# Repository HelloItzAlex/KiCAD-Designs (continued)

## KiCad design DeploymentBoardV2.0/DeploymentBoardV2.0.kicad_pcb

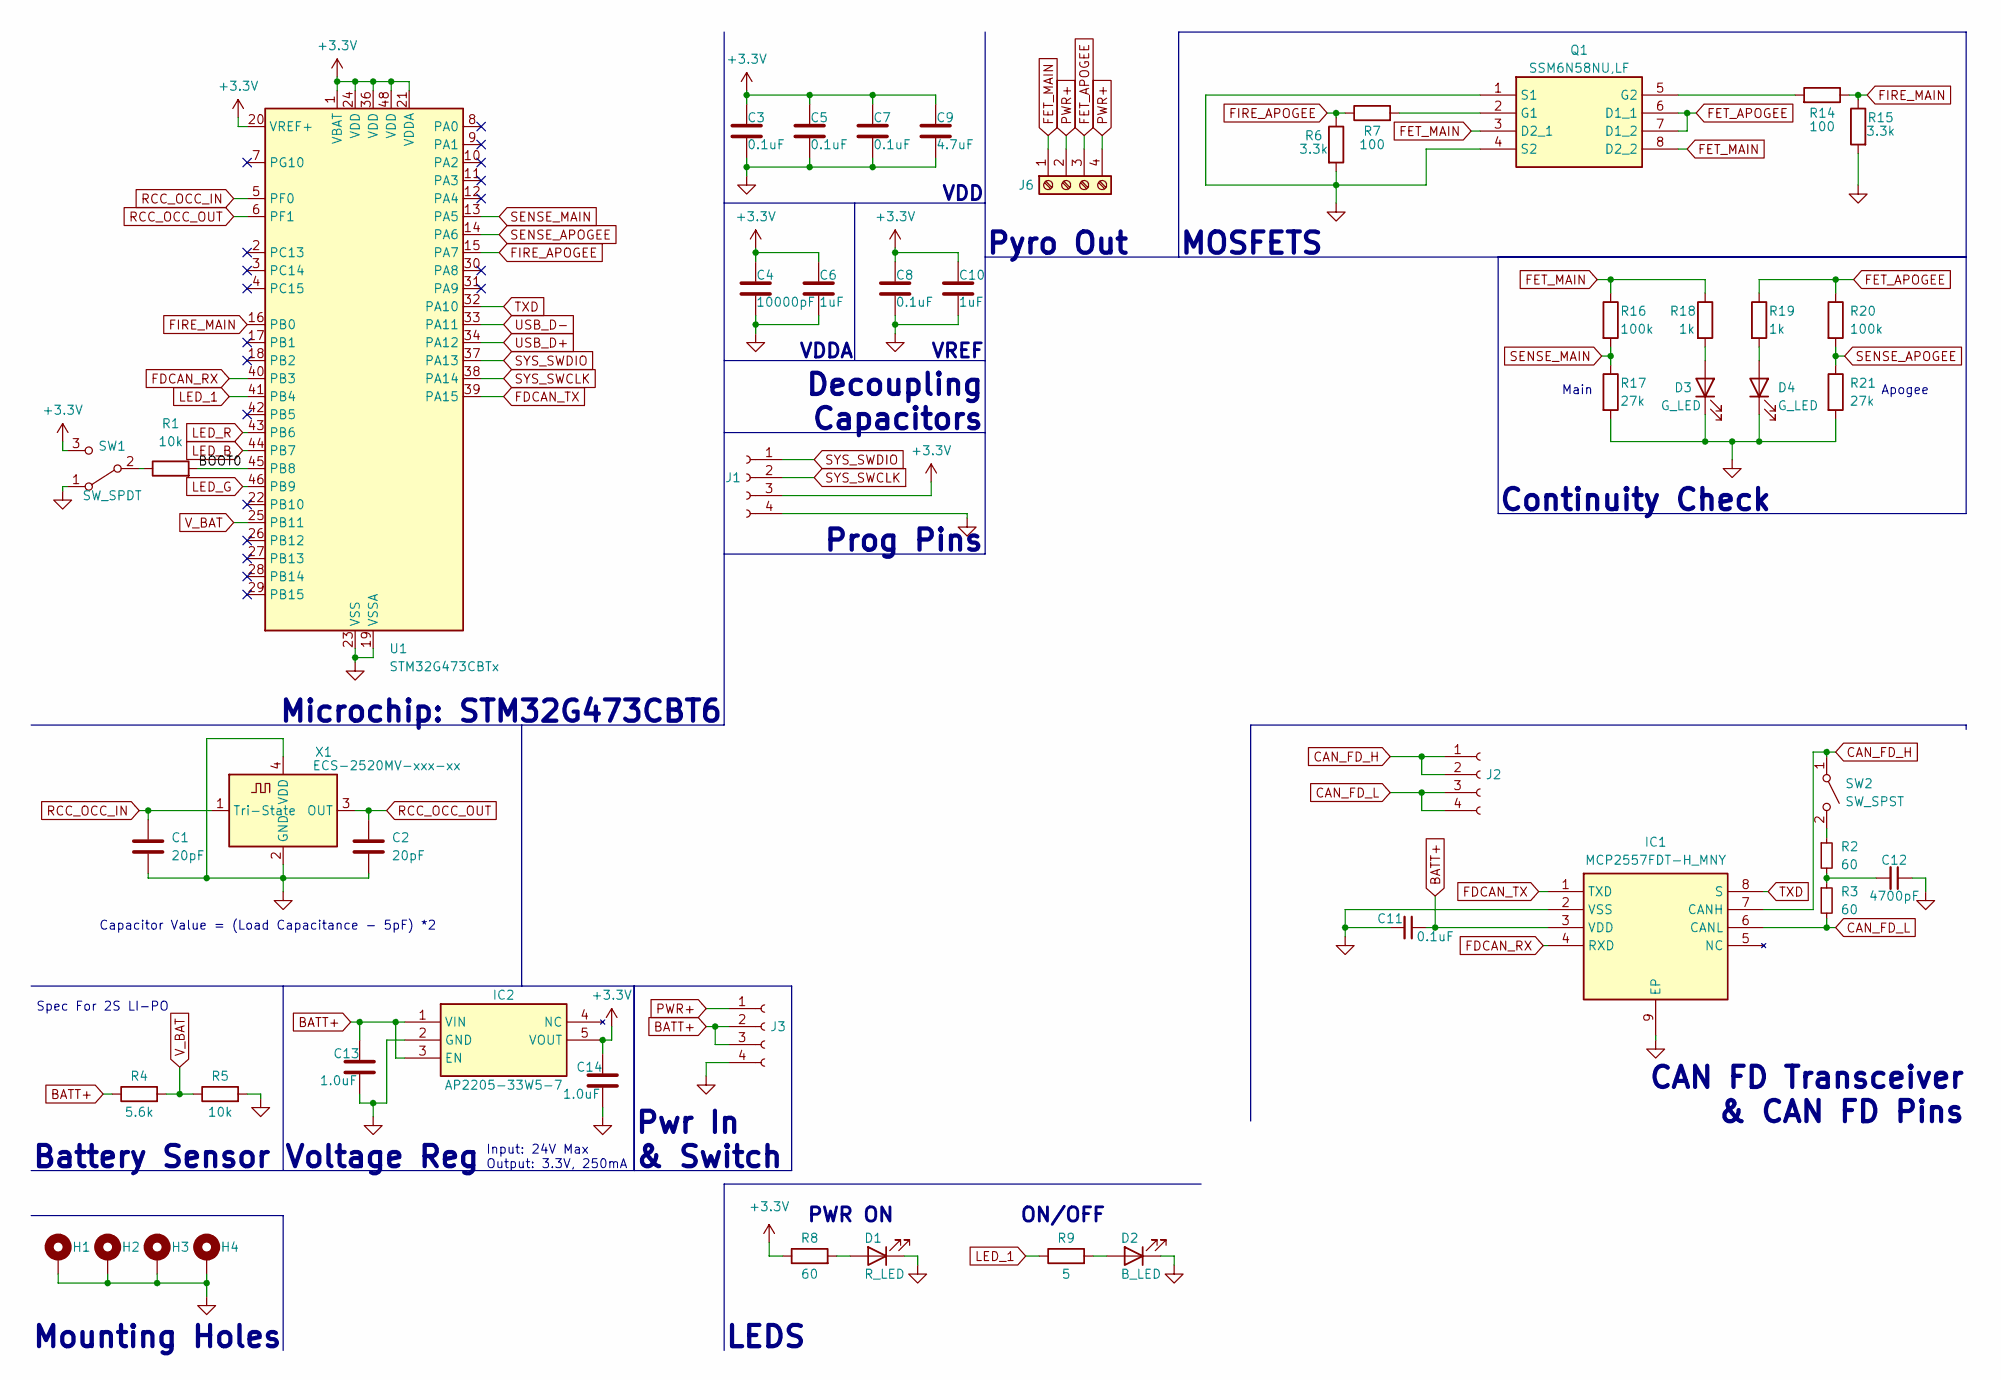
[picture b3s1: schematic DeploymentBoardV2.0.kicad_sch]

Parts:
C1, C2: 20pF; C_0402_1005Metric
C3, C5, C7, C8, C11: 0.1uF; C_0402_1005Metric
C4: 10000pF; C_0402_1005Metric
C6, C10: 1uF; C_0603_1608Metric
C9: 4.7uF; C_0603_1608Metric
C12: 4700pF; C_0402_1005Metric
C13, C14: 1.0uF; C_0402_1005Metric
D1: R_LED; LED_0402_1005Metric
D2: B_LED; LED_0402_1005Metric
D3, D4: G_LED; LED_0402_1005Metric
H1, H2, H3, H4: MountingHole_Pad; MountingHole_2.2mm_M2_ISO7380_Pad
IC1: MCP2557FDT-H_MNY; SON50P300X200X80-9N-D; Mouser Part Number 579-MCP2557FDT-H/MNY
IC2: AP2205-33W5-7; SOT95P282X130-5N; Mouser Part Number 621-AP2205-33W5-7
J1, J2, J3: Conn_01x04_Socket; PinHeader_1x04_P2.54mm_Vertical
J6: PYRO CHANNELS; TerminalBlock_Phoenix_MPT-0,5-4-2.54_1x04_P2.54mm_Horizontal
Q1: SSM6N58NU,LF; SSM6N58NULF; Mouser Part Number 757-SSM6N58NULF
R1, R5: 10k; R_0402_1005Metric
R2, R3: 60; R_0805_2012Metric
R4: 5.6k; R_0402_1005Metric
R6, R15: 3.3k; R_0402_1005Metric
R7, R14: 100; R_0402_1005Metric
R8: 60; R_0402_1005Metric
R9: 5; R_0402_1005Metric
R16, R20: 100k; R_0402_1005Metric
R17, R21: 27k; R_0402_1005Metric
R18, R19: 1k; R_0402_1005Metric
SW1: SW_SPDT; SolderJumper-3_P1.3mm_Open_RoundedPad1.0x1.5mm_NumberLabels
SW2: SW_SPST; SolderJumper-2_P1.3mm_Open_RoundedPad1.0x1.5mm
U1: STM32G473CBTx; LQFP-48_7x7mm_P0.5mm
X1: ECS-2520MV-xxx-xx; Oscillator_SMD_ECS_2520MV-xxx-xx-4Pin_2.5x2.0mm

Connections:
+3.3V: C3.1, C4.1, C5.1, C6.1, C7.1, C8.1, C9.1, C10.1, C14.1, IC2.5 (VOUT), J1.3, R8.1, SW1.3 (C), U1.1 (VBAT), U1.20 (VREF+), U1.21 (VDDA), U1.24 (VDD), U1.36 (VDD), U1.48 (VDD)
/BOOT0: R1.2, U1.45 (PB8)
BATT+: C11.1, C13.1, IC1.3 (VDD), IC2.1 (VIN), IC2.3 (EN), J3.2, J3.3, R4.1
CAN_FD_H: IC1.7 (CANH), J2.1, J2.2, SW2.1 (A)
CAN_FD_L: IC1.6 (CANL), J2.3, J2.4, R3.2
FDCAN_RX: IC1.4 (RXD), U1.40 (PB3)
FDCAN_TX: IC1.1 (TXD), U1.39 (PA15)
FET_APOGEE: J6.3, Q1.6 (D1_1), Q1.7 (D1_2), R19.1, R20.1
FET_MAIN: J6.1, Q1.3 (D2_1), Q1.8 (D2_2), R16.1, R18.1
FIRE_APOGEE: R6.1, R7.1, U1.15 (PA7)
FIRE_MAIN: R14.1, R15.1, U1.16 (PB0)
GND: C1.2, C2.2, C3.2, C4.2, C5.2, C6.2, C7.2, C8.2, C9.2, C10.2, C11.2, C12.1, C13.2, C14.2, D1.1 (K), D2.1 (K), D3.1 (K), D4.1 (K), H1.1, H2.1, H3.1, H4.1, IC1.2 (VSS), IC1.9 (EP), IC2.2 (GND), J1.4, J3.4, Q1.1 (S1), Q1.4 (S2), R5.2, R6.2, R15.2, R17.2, R21.2, SW1.1 (A), U1.19 (VSSA), U1.23 (VSS), U1.35 (VSS), U1.47 (VSS), X1.2 (GND), X1.4 (VDD)
LED_1: R9.1, U1.41 (PB4)
LED_B: U1.44 (PB7)
LED_G: U1.46 (PB9)
LED_R: U1.43 (PB6)
unnamed: C12.2, R2.2, R3.1
unnamed: D1.2 (A), R8.2
unnamed: D2.2 (A), R9.2
unnamed: D3.2 (A), R18.2
unnamed: D4.2 (A), R19.2
unnamed: Q1.2 (G1), R7.2
unnamed: Q1.5 (G2), R14.2
unnamed: R1.1, SW1.2 (B)
unnamed: R2.1, SW2.2 (B)
PWR+: J3.1, J6.2, J6.4
RCC_OCC_IN: C1.1, U1.5 (PF0), X1.1 (Tri-State)
RCC_OCC_OUT: C2.1, U1.6 (PF1), X1.3 (OUT)
SENSE_APOGEE: R20.2, R21.1, U1.14 (PA6)
SENSE_MAIN: R16.2, R17.1, U1.13 (PA5)
SYS_SWCLK: J1.2, U1.38 (PA14)
SYS_SWDIO: J1.1, U1.37 (PA13)
TXD: IC1.8 (S), U1.32 (PA10)
USB_D+: U1.34 (PA12)
USB_D-: U1.33 (PA11)
V_BAT: R4.2, R5.1, U1.25 (PB11)

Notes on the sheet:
Pyro Out
Spec For 2S LI-PO
Decoupling Capacitors
LEDS
Main
MOSFETS
VDD
Capacitor Value = (Load Capacitance - 5pF) *2
Microchip: STM32G473CBT6
Continuity Check
Mounting Holes
Battery Sensor
Apogee
Voltage Reg
Pwr In & Switch
CAN FD Transceiver & CAN FD Pins
Prog Pins
Input: 24V Max Output: 3.3V, 250mA
PWR ON
VDDA
ON/OFF
VREF

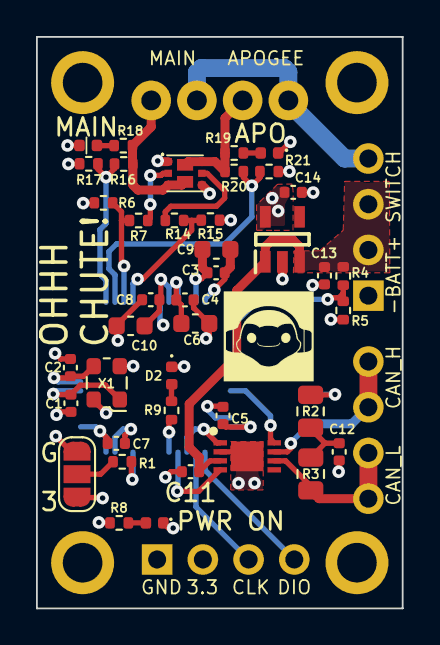
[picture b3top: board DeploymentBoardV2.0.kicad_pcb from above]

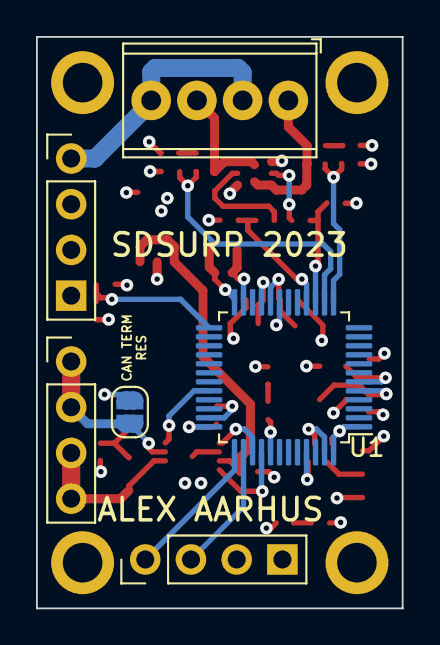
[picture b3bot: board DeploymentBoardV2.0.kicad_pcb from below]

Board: 4 copper layers, 20.3 x 31.8 mm, 50 parts (6 on the bottom side), 31 nets.

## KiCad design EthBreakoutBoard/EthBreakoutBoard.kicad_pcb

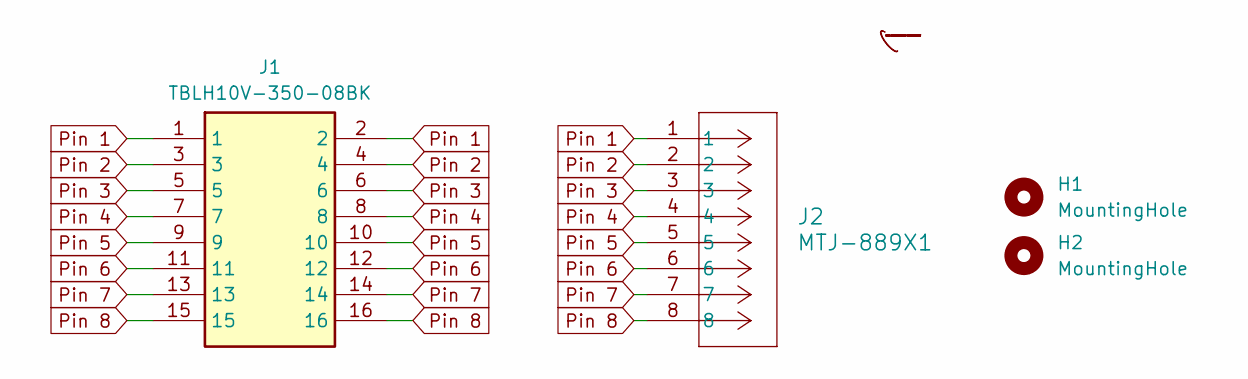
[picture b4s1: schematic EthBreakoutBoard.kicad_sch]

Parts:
H1, H2: MountingHole; MountingHole_3.2mm_M3
J1: TBLH10V-350-08BK; RHDR16W80P550X350_2X8_2870X850X1420P; Mouser Part Number 490-TBLH10V-350-08BK
J2: MTJ-889X1; CONN_MTJ-889X1_ADM

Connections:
Pin 1: J1.1, J1.2, J2.1
Pin 2: J1.3, J1.4, J2.2
Pin 3: J1.5, J1.6, J2.3
Pin 4: J1.7, J1.8, J2.4
Pin 5: J1.9, J1.10, J2.5
Pin 6: J1.11, J1.12, J2.6
Pin 7: J1.13, J1.14, J2.7
Pin 8: J1.15, J1.16, J2.8

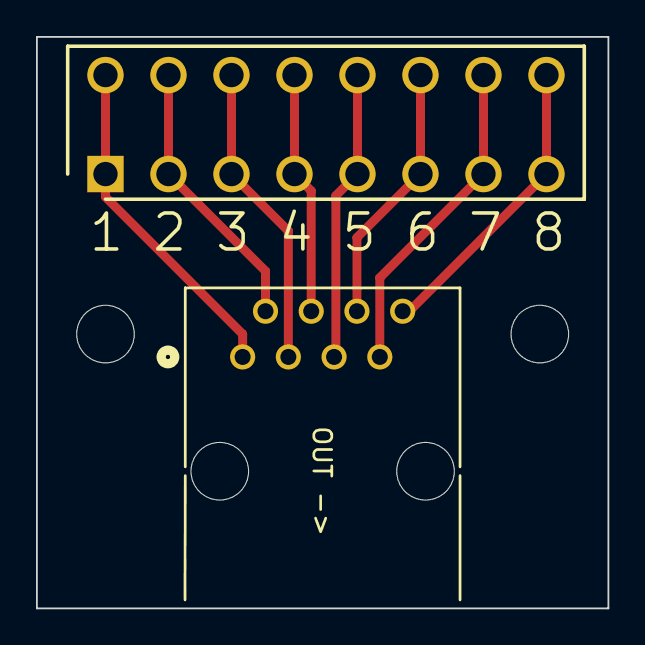
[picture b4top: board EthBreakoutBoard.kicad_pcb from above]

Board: 2 copper layers, 31.8 x 31.8 mm, 4 parts (0 on the bottom side), 8 nets.

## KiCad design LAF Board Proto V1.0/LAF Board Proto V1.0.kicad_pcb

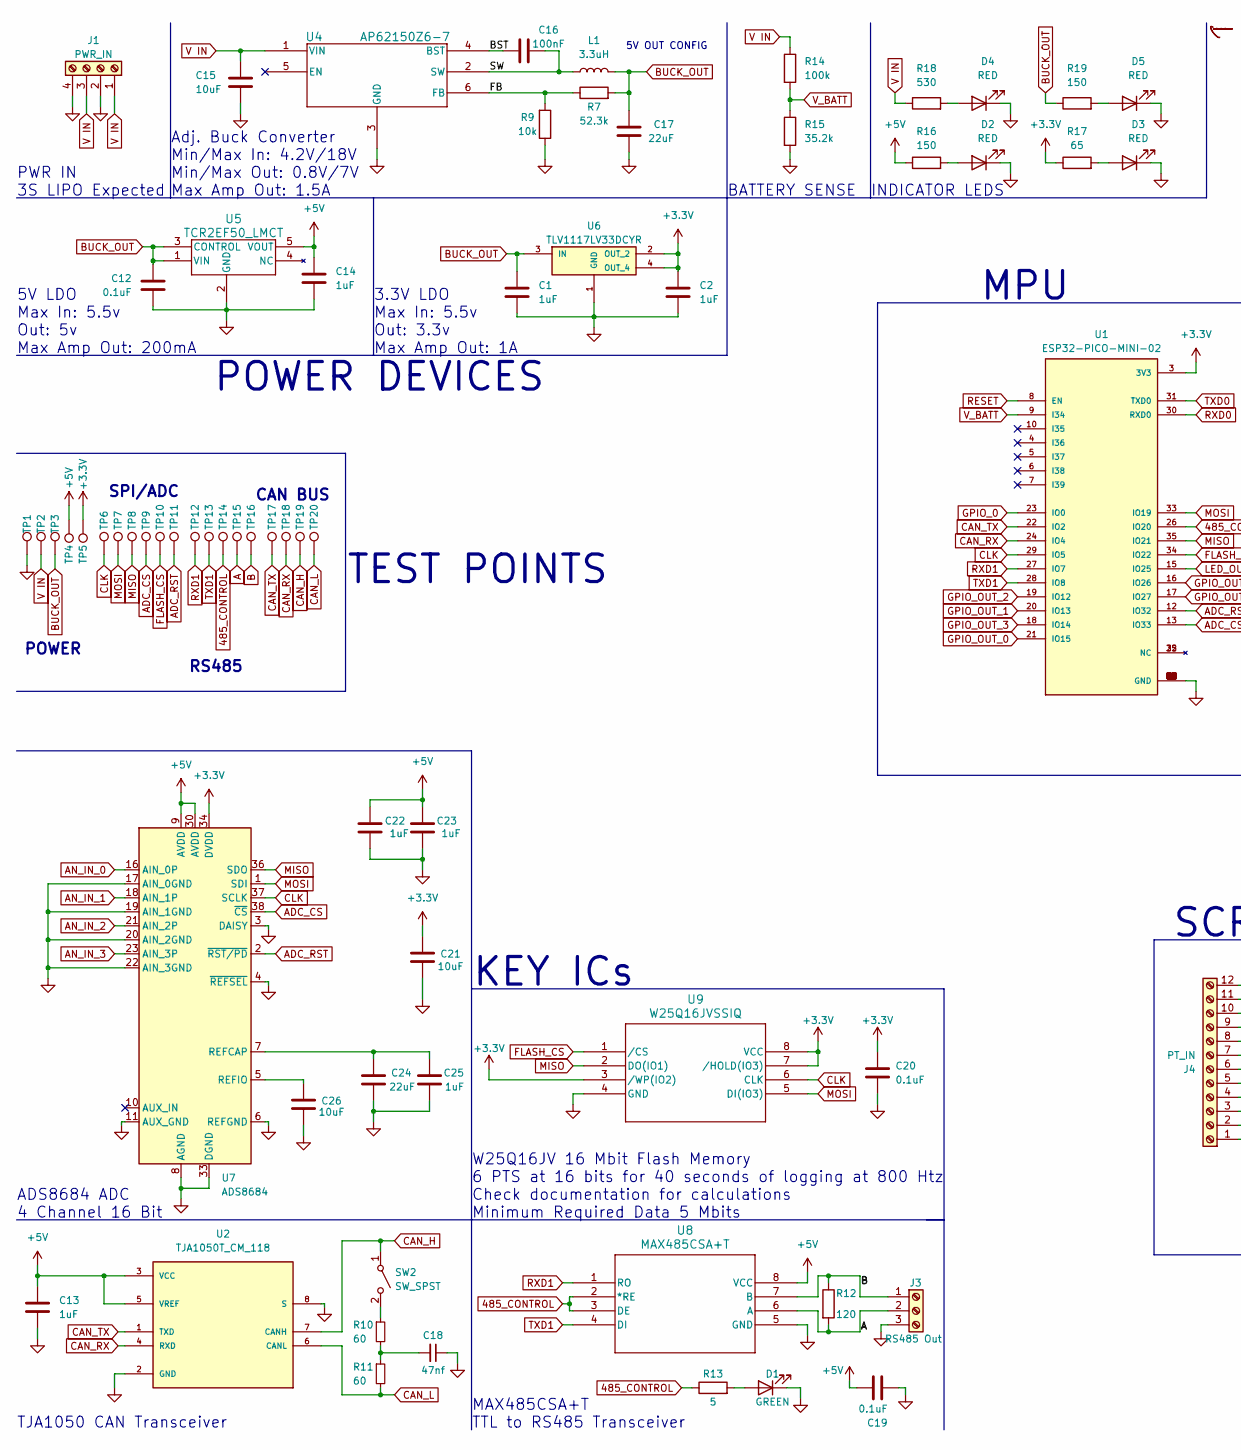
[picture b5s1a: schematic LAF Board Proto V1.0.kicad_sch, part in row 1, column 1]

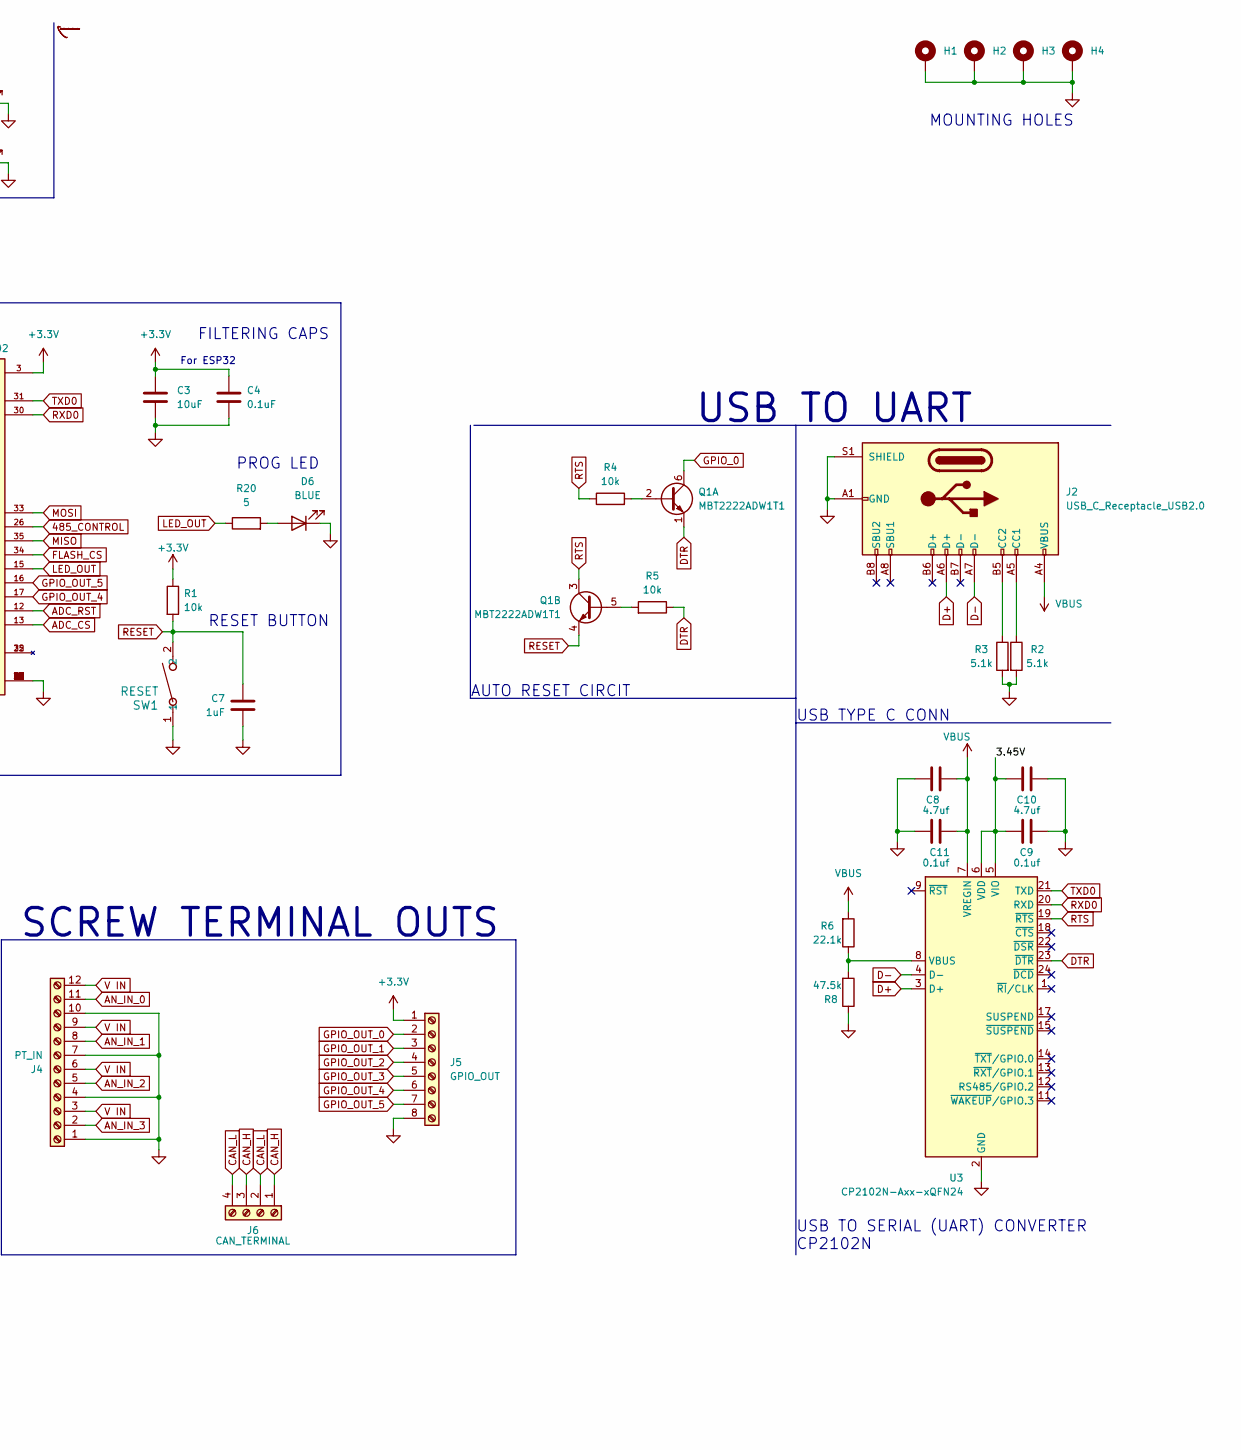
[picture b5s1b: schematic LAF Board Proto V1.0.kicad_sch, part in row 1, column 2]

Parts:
C1, C7, C14, C22, C23, C25: 1uF; C_0603_1608Metric
C2: 1uF; C_0805_2012Metric
C3, C21: 10uF; C_0805_2012Metric
C4, C12: 0.1uF; C_0603_1608Metric
C8, C10: 4.7uf; C_0402_1005Metric
C9, C11: 0.1uf; C_0402_1005Metric
C13: 1uF; C_0402_1005Metric
C15: 10uF; C_0402_1005Metric
C16: 100nF; C_0402_1005Metric
C17: 22uF; C_0402_1005Metric
C18: 47nf; C_0402_1005Metric
C19, C20: 0.1uF; C_0402_1005Metric
C24: 22uF; C_1210_3225Metric
C26: 10uF; C_0603_1608Metric
D1: GREEN; LED_0603_1608Metric
D2, D3, D4, D5: RED; LED_0603_1608Metric
D6: BLUE; LED_0603_1608Metric
H1, H2, H3, H4: MountingHole_Pad; MountingHole_3.2mm_M3_DIN965_Pad
J1: PWR_IN; TerminalBlock_Phoenix_MPT-0,5-4-2.54_1x04_P2.54mm_Horizontal
J2: USB_C_Receptacle_USB2.0; USB_C_Receptacle_HCTL_HC-TYPE-C-16P-01A
J3: RS485 Out; TerminalBlock_Phoenix_MPT-0,5-3-2.54_1x03_P2.54mm_Horizontal
J4: PT_IN; TerminalBlock_Phoenix_MPT-0,5-12-2.54_1x12_P2.54mm_Horizont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
J5: GPIO_OUT; TerminalBlock_Phoenix_MPT-0,5-8-2.54_1x08_P2.54mm_Horizontal
J6: CAN_TERMINAL; TerminalBlock_Phoenix_MPT-0,5-4-2.54_1x04_P2.54mm_Horizontal
L1: 3.3uH; L_1008_2520Metric
Q1: MBT2222ADW1T1; SOT-363_SC-70-6
R1, R4, R5, R9: 10k; R_0402_1005Metric
R2, R3: 5.1k; R_0402_1005Metric
R6: 22.1k; R_0402_1005Metric
R7: 52.3k; R_0402_1005Metric
R8: 47.5k; R_0402_1005Metric
R10, R11: 60; R_0805_2012Metric
R12: 120; R_0805_2012Metric
R13, R20: 5; R_0402_1005Metric
R14: 100k; R_0402_1005Metric
R15: 35.2k; R_0402_1005Metric
R16, R19: 150; R_0402_1005Metric
R17: 65; R_0402_1005Metric
R18: 530; R_0402_1005Metric
SW1: RESET; SW_PTS636_CNK
SW2: SW_SPST; SolderJumper-2_P1.3mm_Open_RoundedPad1.0x1.5mm
TP1, TP2, TP3, TP4, TP5, TP6, TP7, TP8, TP9, TP10, TP11, TP12, TP13, TP14, TP15, TP16, TP17, TP18, TP19, TP20: TestPoint; TestPoint_Loop_D1.80mm_Drill1.0mm_Beaded
U1: ESP32-PICO-MINI-02; MODULE_ESP32-PICO-MINI-02; PARTREV v1.0
U2: TJA1050T_CM_118; SOIC127P600X175-8N; PARTREV 4
U3: CP2102N-Axx-xQFN24; QFN-24-1EP_4x4mm_P0.5mm_EP2.7x2.7mm
U4: AP62150Z6-7; TSOT-23-6
U5: TCR2EF50_LMCT; SOT_EF50_LMCT_TOS
U6: TLV1117LV33DCYR; VREG_TLV1117LV33DCYR; PARTREV B
U7: ADS8684; TSSOP-38_4.4x9.7mm_P0.5mm
U8: MAX485CSA+T; 21-0041-3-M_90-0096-8L_MXM
U9: W25Q16JVSSIQ; W25Q16JVSSIQ_WIN

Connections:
485_CONTROL: R13.1, TP14.1, U1.26 (IO20), U8.2 (*RE), U8.3 (DE)
+3.3V: C2.1, C3.1, C4.1, C20.1, C21.2, J5.1, R1.1, R17.1, TP5.1, U1.3 (3V3), U6.2 (OUT_2), U6.4 (OUT_4), U7.34 (DVDD), U9.3 (/WP(IO2)), U9.7 (/HOLD(IO3)), U9.8 (VCC)
+5V: C13.1, C14.1, C19.1, C22.2, C23.2, R16.1, TP4.1, U2.3 (VCC), U2.5 (VREF), U5.5 (VOUT), U7.9 (AVDD), U7.30 (AVDD), U8.8 (VCC)
/3.45V: C9.1, C10.1, U3.5 (VIO), U3.6 (VDD)
/BST: C16.1, U4.4 (BST)
/FB: R7.1, R9.2, U4.6 (FB)
/SW: C16.2, L1.1, U4.2 (SW)
A: J3.2, R12.2, TP15.1, U8.6 (A)
ADC_CS: TP9.1, U1.13 (IO33), U7.38 (~CS)
ADC_RST: TP11.1, U1.12 (IO32), U7.2 (~RST/PD)
AN_IN_0: J4.11, U7.16 (AIN_0P)
AN_IN_1: J4.8, U7.18 (AIN_1P)
AN_IN_2: J4.5, U7.21 (AIN_2P)
AN_IN_3: J4.2, U7.23 (AIN_3P)
B: J3.1, R12.1, TP16.1, U8.7 (B)
BUCK_OUT: C1.1, C12.1, C17.1, L1.2, R7.2, R19.1, TP3.1, U5.1 (VIN), U5.3 (CONTROL), U6.3 (IN)
CAN_H: J6.1, J6.3, SW2.1 (A), TP19.1, U2.7 (CANH)
CAN_L: J6.2, J6.4, R11.2, TP20.1, U2.6 (CANL)
CAN_RX: TP18.1, U1.24 (IO4), U2.4 (RXD)
CAN_TX: TP17.1, U1.22 (IO2), U2.1 (TXD)
CLK: TP6.1, U1.29 (IO5), U7.37 (SCLK), U9.6 (CLK)
D+: J2.A6 (D+), U3.3 (D+)
D-: J2.A7 (D-), U3.4 (D-)
DTR: Q1.1 (E1), R5.1, U3.23 (~DTR)
FLASH_CS: TP10.1, U1.34 (IO22), U9.1 (/CS)
GND: C1.2, C2.2, C3.2, C4.2, C7.2, C8.2, C9.2, C10.2, C11.2, C12.2, C13.2, C14.2, C15.2, C17.2, C18.1, C19.2, C20.2, C21.1, C22.1, C23.1, C24.1, C25.1, C26.2, D1.1 (K), D2.1 (K), D3.1 (K), D4.1 (K), D5.1 (K), D6.1 (K), H1.1, H2.1, H3.1, H4.1, J1.2, J1.4, J2.A1 (GND), J2.A12 (GND), J2.B1 (GND), J2.B12 (GND), J2.S1 (SHIELD), J3.3, J4.1, J4.4, J4.7, J4.10, J5.8, R2.2, R3.2, R8.1, R9.1, R15.2, SW1.1, TP1.1, U1.1 (GND), U1.2 (GND), U1.11 (GND), U1.14 (GND), U1.36 (GND), U1.37 (GND), U1.38 (GND), U1.39 (GND), U1.40 (GND), U1.41 (GND), U1.42 (GND), U1.43 (GND), U1.44 (GND), U1.45 (GND), U1.46 (GND), U1.47 (GND), U1.48 (GND), U1.49 (GND), U1.50 (GND), U1.51 (GND), U1.52 (GND), U1.53 (GND), U1.54 (GND), U1.55 (GND), U1.56 (GND), U1.57 (GND), U1.58 (GND), U1.59 (GND), U1.60 (GND), U1.61 (GND), U2.2 (GND), U2.8 (S), U3.2 (GND), U3.25 (GND), U4.3 (GND), U5.2 (GND), U6.1 (GND), U7.3 (DAISY), U7.4 (~REFSEL), U7.6 (REFGND), U7.8 (AGND), U7.11 (AUX_GND), U7.17 (AIN_0GND), U7.19 (AIN_1GND), U7.20 (AIN_2GND), U7.22 (AIN_3GND), U7.28 (AGND), U7.29 (AGND), U7.31 (AGND), U7.32 (AGND), U7.33 (DGND), U8.5 (GND), U9.4 (GND)
GPIO_0: Q1.6 (C1), U1.23 (IO0)
GPIO_OUT_0: J5.2, U1.21 (IO15)
GPIO_OUT_1: J5.3, U1.20 (IO13)
GPIO_OUT_2: J5.4, U1.19 (IO12)
GPIO_OUT_3: J5.5, U1.18 (IO14)
GPIO_OUT_4: J5.6, U1.17 (IO27)
GPIO_OUT_5: J5.7, U1.16 (IO26)
LED_OUT: R20.1, U1.15 (IO25)
MISO: TP8.1, U1.35 (IO21), U7.36 (SDO), U9.2 (DO(IO1))
MOSI: TP7.1, U1.33 (IO19), U7.1 (SDI), U9.5 (DI(IO3))
unnamed: C18.2, R10.2, R11.1
unnamed: D1.2 (A), R13.2
unnamed: D2.2 (A), R16.2
unnamed: D3.2 (A), R17.2
unnamed: D4.2 (A), R18.2
unnamed: D5.2 (A), R19.2
unnamed: D6.2 (A), R20.2
unnamed: J2.A5 (CC1), R2.1
unnamed: J2.B5 (CC2), R3.1
unnamed: Q1.2 (B1), R4.2
unnamed: Q1.5 (B2), R5.2
unnamed: R10.1, SW2.2 (B)
unnamed: R6.1, R8.2, U3.8 (VBUS)
unnamed: C24.2, C25.2, U7.7 (REFCAP)
unnamed: C26.1, U7.5 (REFIO)
RESET: C7.1, Q1.4 (E2), R1.2, SW1.2, U1.8 (EN)
RTS: Q1.3 (C2), R4.1, U3.19 (~RTS)
RXD0: U1.30 (RXD0), U3.20 (RXD)
RXD1: TP12.1, U1.27 (IO7), U8.1 (RO)
TXD0: U1.31 (TXD0), U3.21 (TXD)
TXD1: TP13.1, U1.28 (IO8), U8.4 (DI)
V IN: C15.1, J1.1, J1.3, J4.3, J4.6, J4.9, J4.12, R14.1, R18.1, TP2.1, U4.1 (VIN)
VBUS: C8.1, C11.1, J2.A4 (VBUS), J2.A9 (VBUS), J2.B4 (VBUS), J2.B9 (VBUS), R6.2, U3.7 (VREGIN)
V_BATT: R14.2, R15.1, U1.9 (I34)

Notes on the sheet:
BATTERY SENSE
MPU
For ESP32
USB TO UART
TEST POINTS
USB TO SERIAL (UART) CONVERTER CP2102N
RESET BUTTON
POWER
ADS8684 ADC 4 Channel 16 Bit
Adj. Buck Converter Min/Max In: 4.2V/18V Min/Max Out: 0.8V/7V Max Amp Out: 1.5A
SCREW TERMINAL OUTS
W25Q16JV 16 Mbit Flash Memory 6 PTS at 16 bits for 40 seconds of logging at 800 Htz Check documentation for calculations Minimum Required Data 5 Mbits
SPI/ADC
FILTERING CAPS
MAX485CSA+T TTL to RS485 Transceiver
3.3V LDO Max In: 5.5v Out: 3.3v Max Amp Out: 1A
TJA1050 CAN Transceiver
RS485
PROG LED
INDICATOR LEDS
CAN BUS
POWER DEVICES
AUTO RESET CIRCIT
PWR IN 3S LIPO Expected
5V LDO Max In: 5.5v Out: 5v Max Amp Out: 200mA
USB TYPE C CONN
MOUNTING HOLES
5V OUT CONFIG
KEY ICs

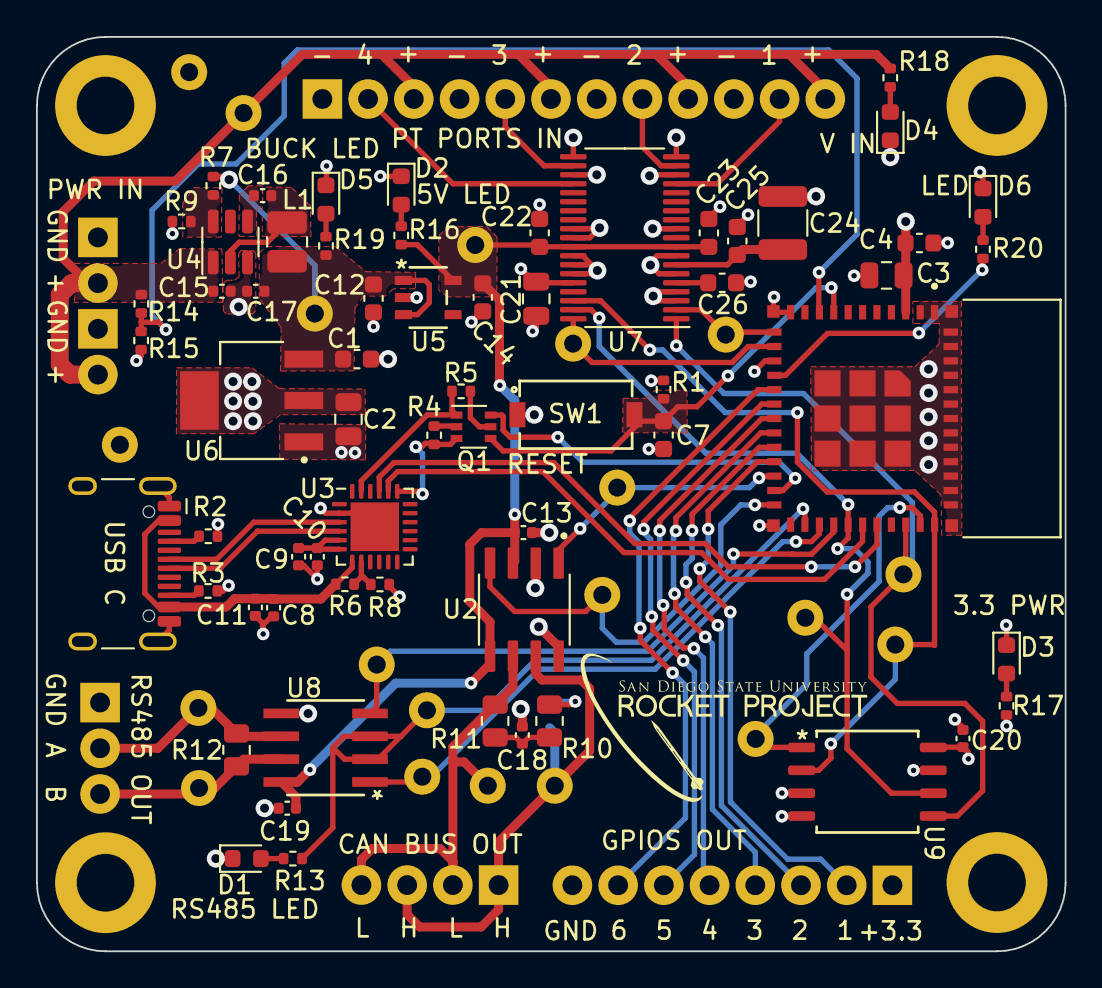
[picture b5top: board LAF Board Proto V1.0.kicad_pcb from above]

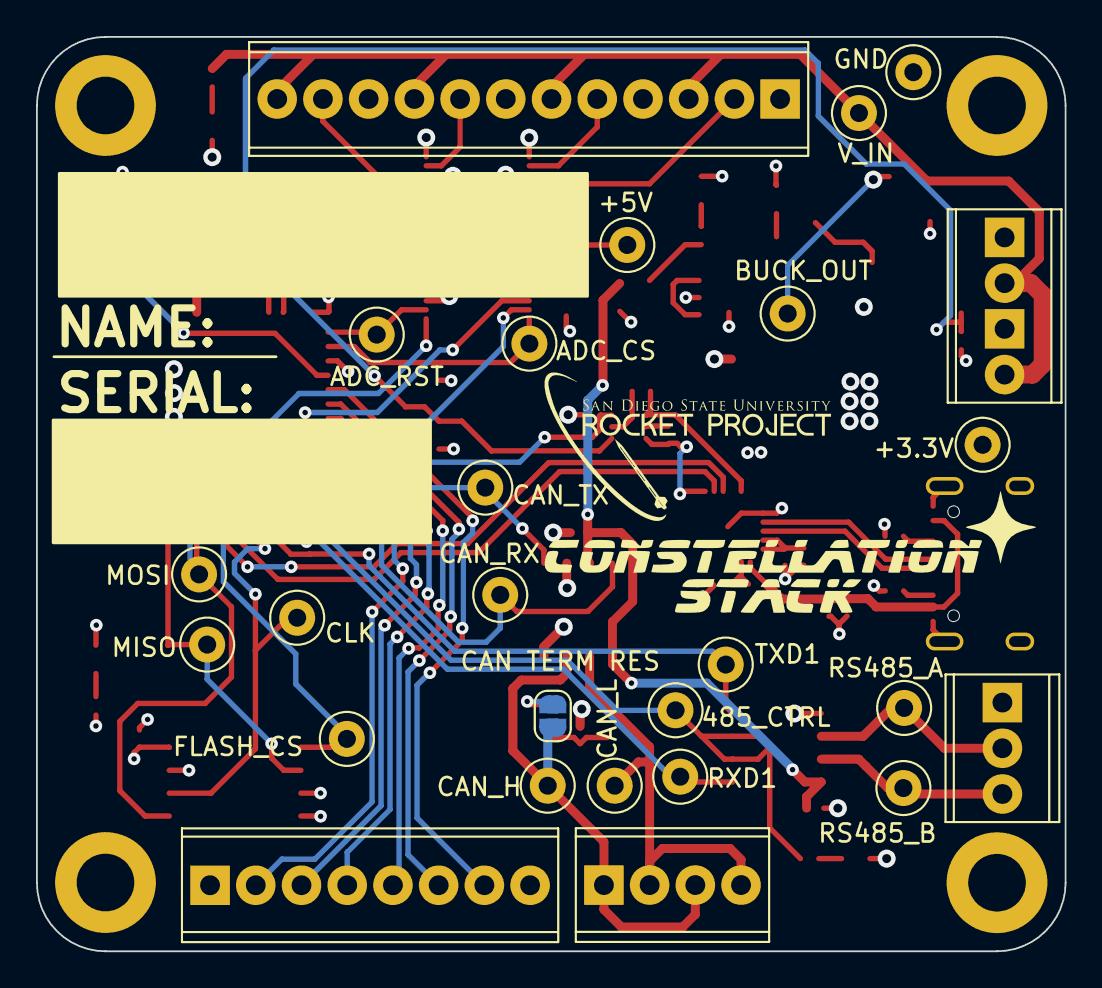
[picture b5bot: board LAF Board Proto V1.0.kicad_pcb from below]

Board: 4 copper layers, 57.1 x 50.8 mm, 93 parts (26 on the bottom side), 60 nets.

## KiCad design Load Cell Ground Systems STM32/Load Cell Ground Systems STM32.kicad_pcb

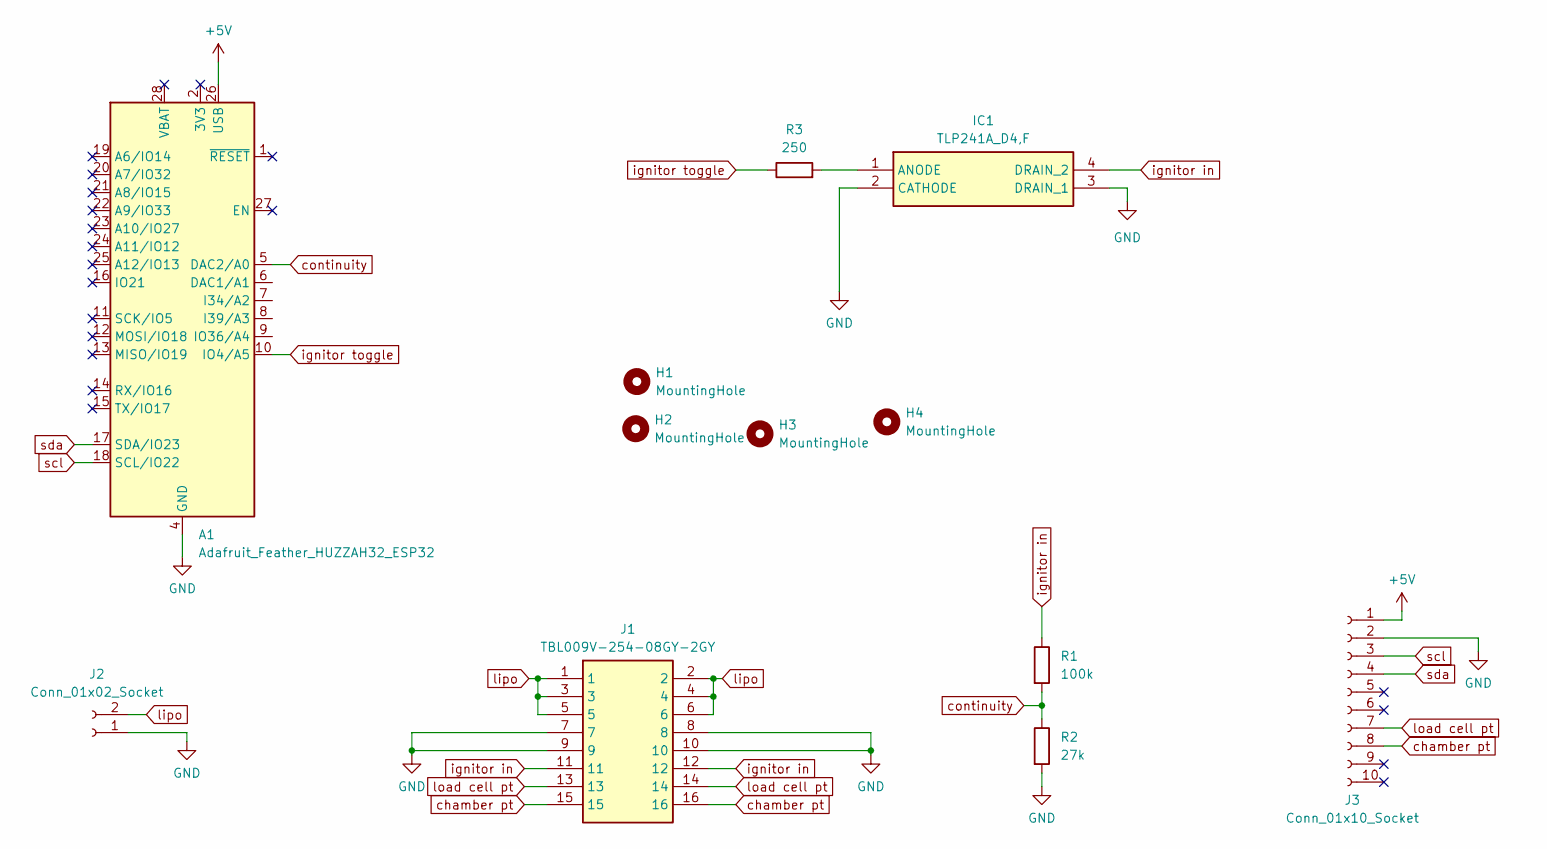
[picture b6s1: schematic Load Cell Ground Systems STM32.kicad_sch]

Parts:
A1: Adafruit_Feather_HUZZAH32_ESP32; Adafruit_Feather
H1, H2, H3, H4: MountingHole; MountingHole_3.2mm_M3
IC1: TLP241A_D4,F; DIP762W60P254L458H485Q4N; Mouser Part Number 757-TLP241AD4F
J1: TBL009V-254-08GY-2GY; RHDR16W70P508X254_2X8_2182X1000X1655P; Mouser Part Number 490-TBL09V25408GY2GY
J2: Conn_01x02_Socket; PinSocket_1x02_P2.54mm_Vertical
J3: Conn_01x10_Socket; PinSocket_1x10_P2.54mm_Vertical
R1: 100k; R_Axial_DIN0204_L3.6mm_D1.6mm_P5.08mm_Horizontal
R2: 27k; R_Axial_DIN0204_L3.6mm_D1.6mm_P5.08mm_Horizontal
R3: 250; R_Axial_DIN0204_L3.6mm_D1.6mm_P5.08mm_Horizontal

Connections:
+5V: A1.26 (USB), J3.1
GND: A1.4 (GND), IC1.2 (CATHODE), IC1.3 (DRAIN_1), J1.7, J1.8, J1.9, J1.10, J2.1, J3.2, R2.2
unnamed: IC1.1 (ANODE), R3.2
chamber pt: J1.15, J1.16, J3.8
continuity: A1.5 (DAC2/A0), R1.2, R2.1
ignitor in: IC1.4 (DRAIN_2), J1.11, J1.12, R1.1
ignitor toggle: A1.10 (IO4/A5), R3.1
lipo: J1.1, J1.2, J1.3, J1.4, J1.5, J1.6, J2.2
load cell pt: J1.13, J1.14, J3.7
scl: A1.18 (SCL/IO22), J3.3
sda: A1.17 (SDA/IO23), J3.4

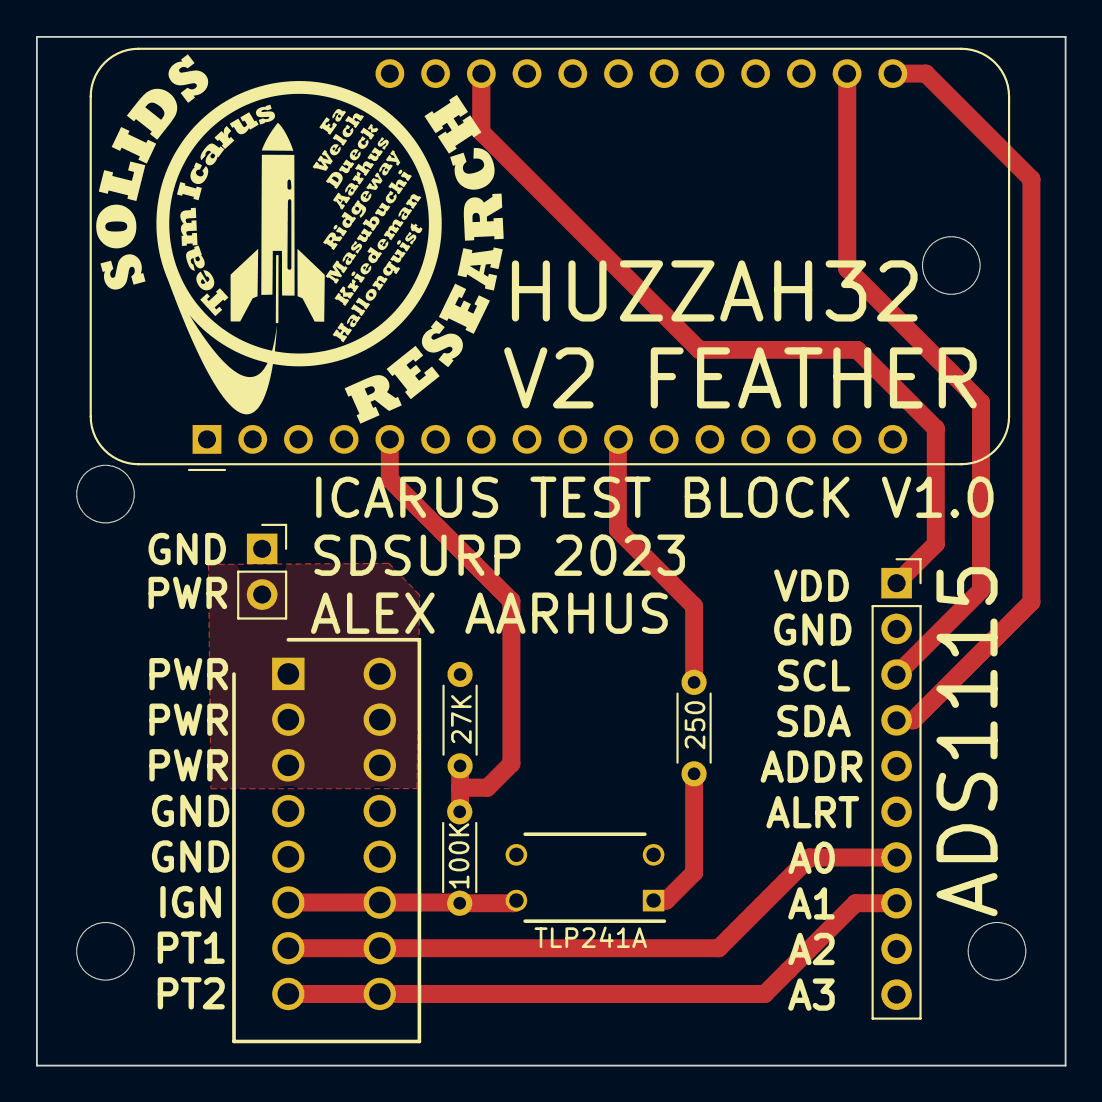
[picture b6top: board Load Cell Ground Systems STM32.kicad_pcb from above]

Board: 2 copper layers, 57.1 x 57.1 mm, 12 parts (0 on the bottom side), 11 nets.

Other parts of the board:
Hv: MountingHole; MountingHole_3.2mm_M3

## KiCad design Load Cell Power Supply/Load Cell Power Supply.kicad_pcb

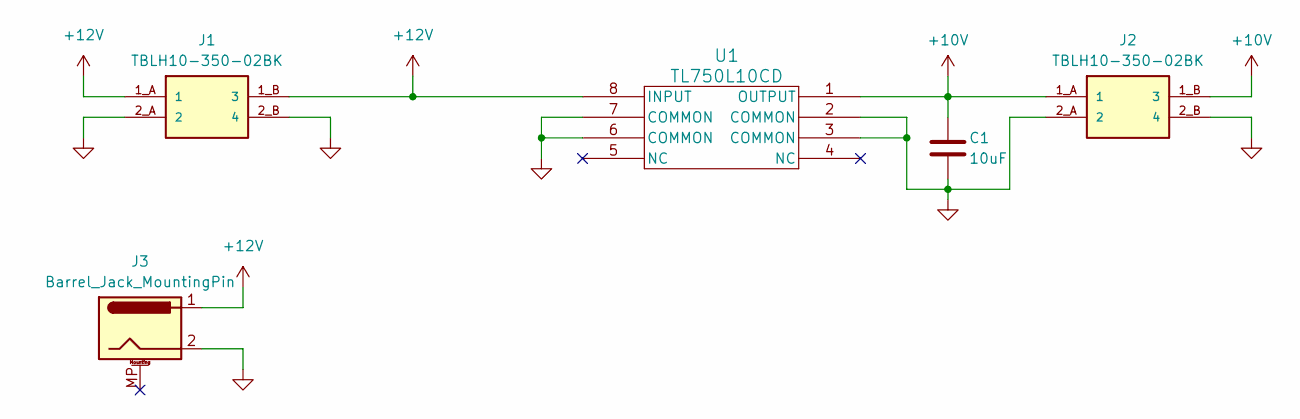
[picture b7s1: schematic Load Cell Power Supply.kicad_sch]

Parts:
C1: 10uF; C_01005_0402Metric_Pad0.57x0.30mm_HandSolder
J1, J2: TBLH10-350-02BK; CUI_TBLH10-350-02BK
J3: Barrel_Jack_MountingPin; BarrelJack_CLIFF_FC681465S_SMT_Horizontal
U1: TL750L10CD; D8_TEX

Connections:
+10V: C1.1, J2.1_A (1), J2.1_B (3), U1.1 (OUTPUT)
+12V: J1.1_A (1), J1.1_B (3), J3.1, U1.8 (INPUT)
GND: C1.2, J1.2_A (2), J1.2_B (4), J2.2_A (2), J2.2_B (4), J3.2, U1.2 (COMMON), U1.3 (COMMON), U1.6 (COMMON), U1.7 (COMMON)

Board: 2 copper layers, 5 parts (0 on the bottom side), 3 nets, no tracks yet.
